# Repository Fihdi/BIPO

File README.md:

# 8hp Dual Bipolar-VCAs / Ring modulators

BIPO consists of two VCAs which can be used individually or locked together to allow for sidechaining / crossfading. Changing the LEVEL, the VCAs can be biased as to allow each section to be used as a ringmodulator. The resulting ringmodulated signal of the input and the CV is available at the BIPO outputs. The VCA outputs are always summed together at the MIX output.

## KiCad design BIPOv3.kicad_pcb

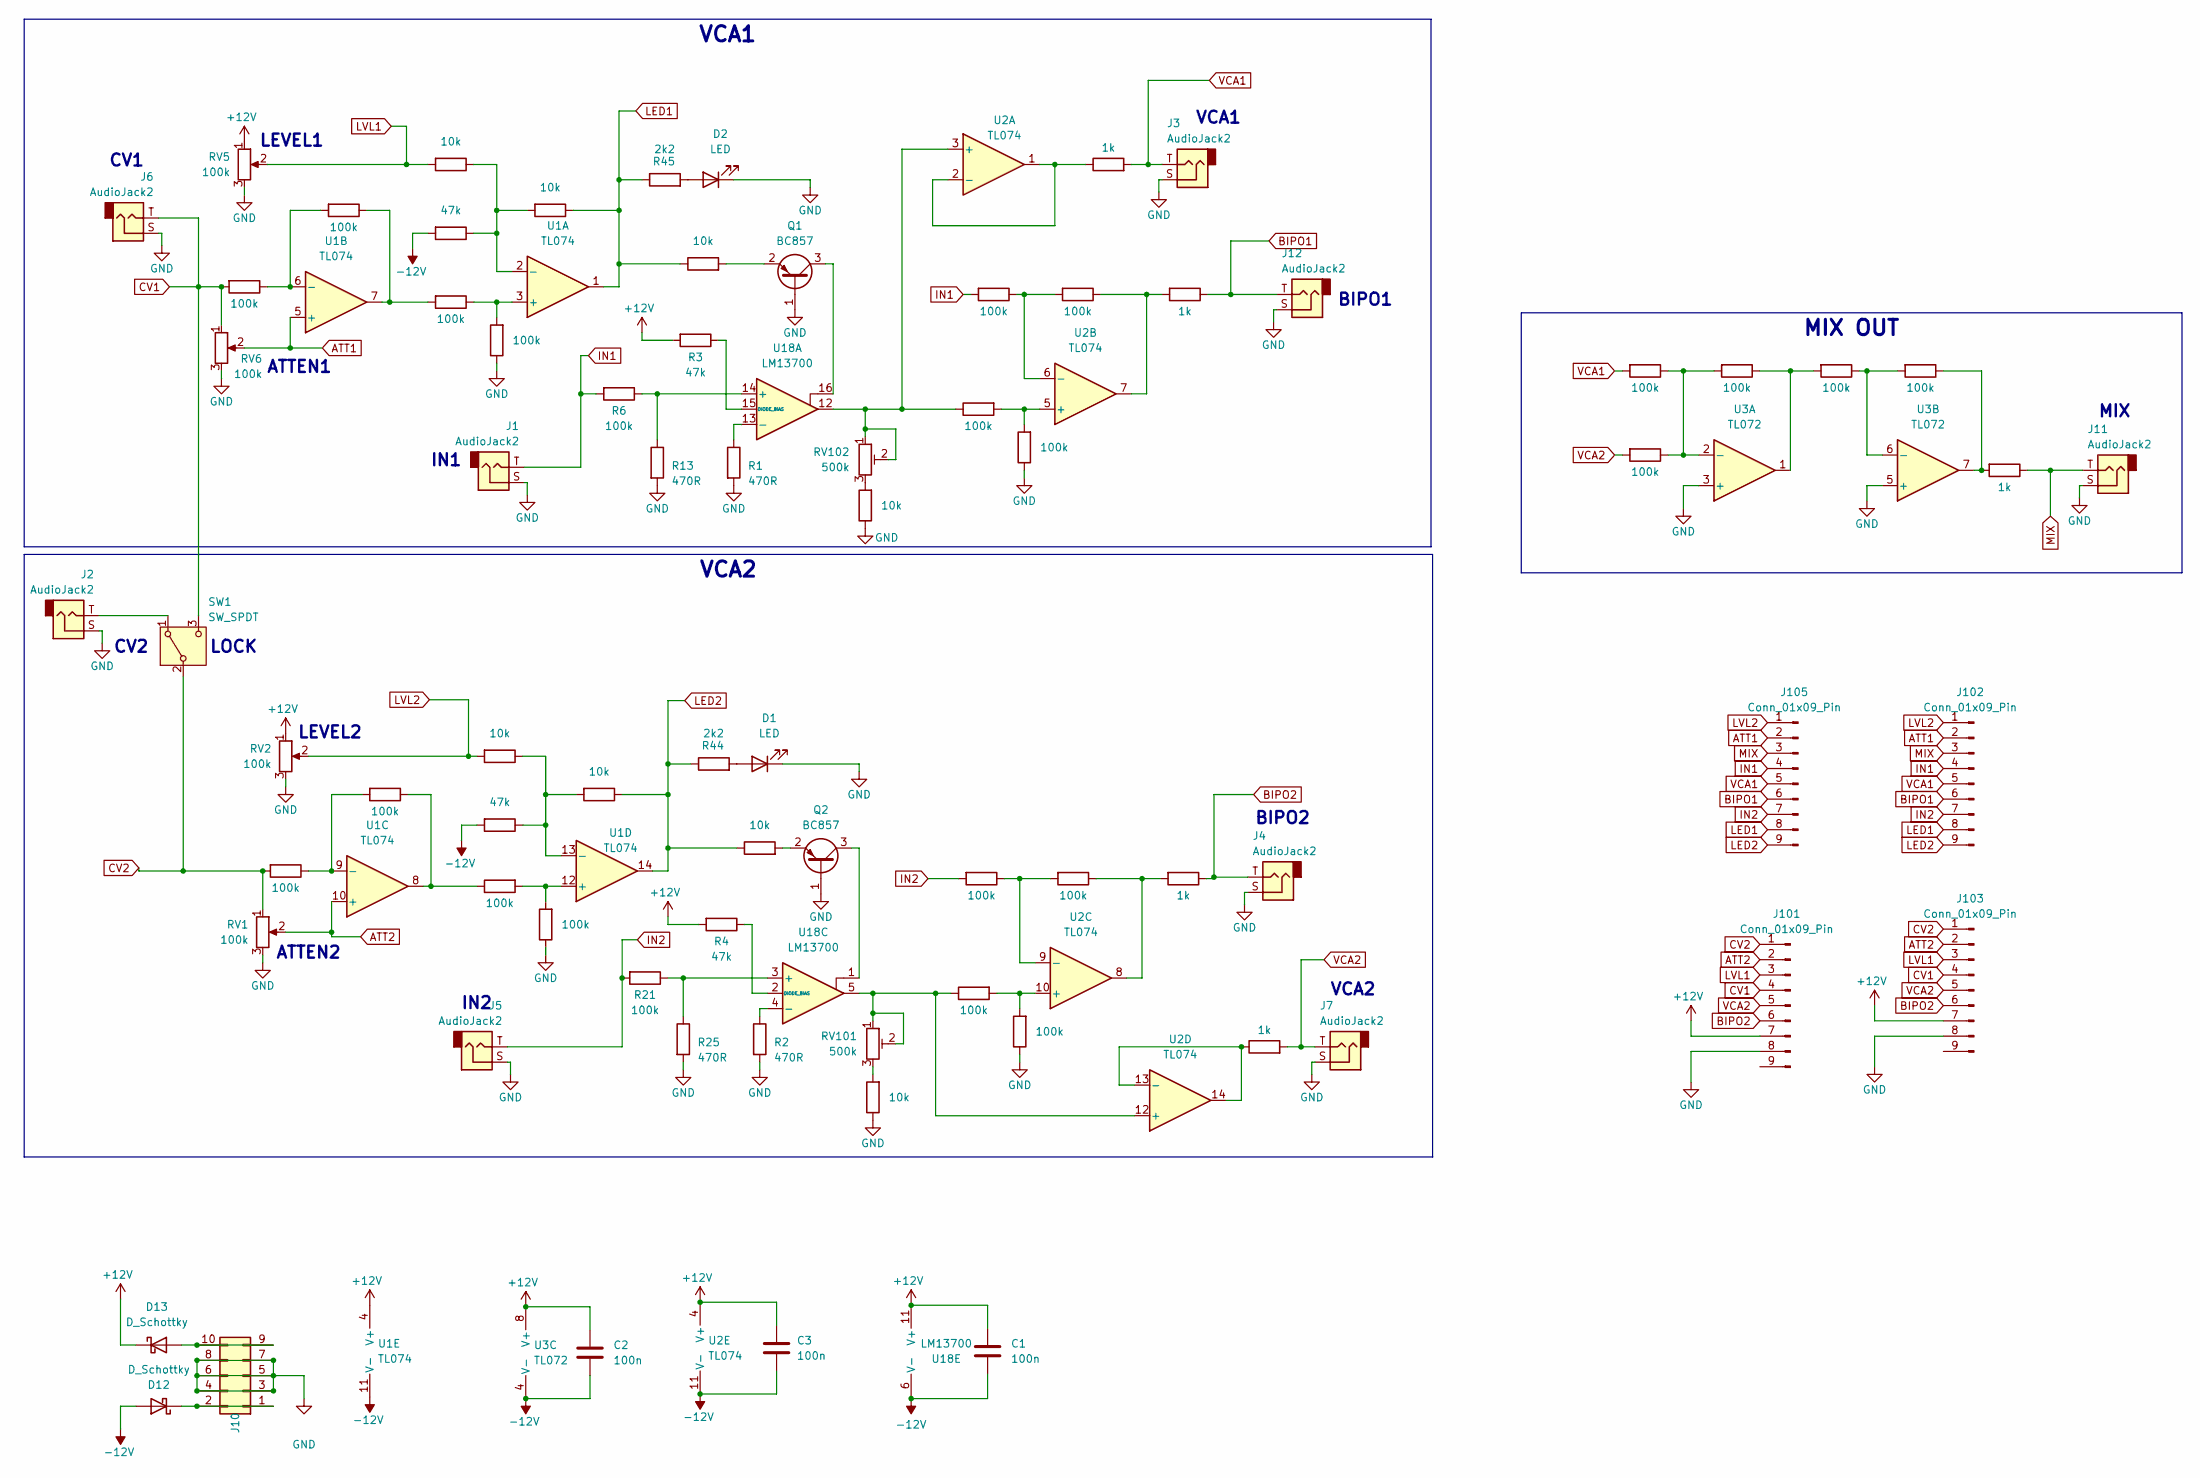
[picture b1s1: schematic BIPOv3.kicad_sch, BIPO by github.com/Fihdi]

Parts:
C1, C2, C3: 100n; C_1206_3216Metric
D1, D2: LED; LED_D3.0mm
D12, D13: D_Schottky; D_SOD-323_HandSoldering
J1, J2, J3, J4, J5, J6, J7, J11, J12: AudioJack2; MonoTRS
J10: Conn_02x05_Odd_Even; IDC-Header_2x05_P2.54mm_Vertical
J101, J102, J103, J105: Conn_01x09_Pin; PinHeader_1x09_P2.54mm_Vertical
Q1, Q2: BC857; SOT-23
R1, R2, R13, R25: 470R; R_1206_3216Metric
R3, R4, R10, R22: 47k; R_1206_3216Metric
R5, R7, R11, R12, R20, R26, R28, R83: 10k; R_1206_3216Metric
R6, R8, R9, R14, R15, R16, R17, R18, R19, R21, R23, R24, R27, R29, R30, R31, R32, R34, R35, R38, R39, R41, R42: 100k; R_1206_3216Metric
R33, R36, R37, R40, R43: 1k; R_1206_3216Metric
R44, R45: 2k2; R_1206_3216Metric
RV1, RV2, RV5, RV6: 100k; Potentiometer_Alpha_RD901F-40-00D_Single_Vertical
RV101, RV102: 500k; Potentiometer_Bourns_3266Y_Vertical
SW1: SW_SPDT; Switch
U1, U2: TL074; SOIC-14_3.9x8.7mm_P1.27mm
U3: TL072; SOIC-8_3.9x4.9mm_P1.27mm
U18: LM13700; SOIC-16_3.9x9.9mm_P1.27mm

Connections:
+12V: C1.1, C2.1, C3.1, D13.1 (K), J101.7, J103.7, R3.2, R4.2, RV2.1, RV5.1, U1.4 (V+), U2.4 (V+), U3.8 (V+), U18.11 (V+)
-12V: C1.2, C2.2, C3.2, D12.2 (A), R10.2, R22.2, U1.11 (V-), U2.11 (V-), U3.4 (V-), U18.6 (V-)
ATT1: J102.2, J105.2, RV6.2, U1.5 (+)
ATT2: J101.2, J103.2, RV1.2, U1.10 (+)
BIPO1: J12.T, J102.6, J105.6, R36.1
BIPO2: J4.T, J101.6, J103.6, R33.1
CV1: J6.T, J101.4, J103.4, R15.2, RV6.1, SW1.3 (C)
CV2: J101.1, J103.1, R18.2, RV1.1, SW1.2 (B)
GND: D1.1 (K), D2.1 (K), J1.S, J2.S, J3.S, J4.S, J5.S, J6.S, J7.S, J10.3, J10.4, J10.5, J10.6, J10.7, J10.8, J11.S, J12.S, J101.8, J103.8, Q1.1 (B), Q2.1 (B), R1.2, R2.2, R5.1, R7.1, R8.1, R13.2, R24.1, R25.2, R39.1, R42.1, RV1.3, RV2.3, RV5.3, RV6.3, U3.3 (+), U3.5 (+)
IN1: J1.T, J102.4, J105.4, R6.2, R17.2
IN2: J5.T, J102.7, J105.7, R21.2, R34.2
LED1: J102.8, J105.8, R11.1, R45.1, R83.1, U1.1
LED2: J102.9, J105.9, R26.1, R28.1, R44.1, U1.14
LVL1: J101.3, J103.3, R12.2, RV5.2
LVL2: J102.1, J105.1, R20.2, RV2.2
MIX: J11.T, J102.3, J105.3, R37.1
unnamed: D1.2 (A), R44.2
unnamed: D2.2 (A), R45.2
unnamed: D12.1 (K), J10.1, J10.2
unnamed: D13.2 (A), J10.9, J10.10
unnamed: Q1.3 (C), U18.16
unnamed: Q1.2 (E), R83.2
unnamed: Q2.3 (C), U18.1
unnamed: Q2.2 (E), R28.2
unnamed: R5.2, RV102.3
unnamed: R7.2, RV101.3
unnamed: R9.2, R14.1, U1.7
unnamed: R16.1, R36.2, U2.7
unnamed: R19.1, R23.1, U1.8
unnamed: R29.1, R30.2, U3.1
unnamed: R31.1, R37.2, U3.7
unnamed: R33.2, R35.1, U2.8
unnamed: J2.T, SW1.1 (A)
unnamed: R8.2, R9.1, U1.3 (+)
unnamed: R10.1, R11.2, R12.1, U1.2 (-)
unnamed: R14.2, R15.1, U1.6 (-)
unnamed: R18.1, R19.2, U1.9 (-)
unnamed: R23.2, R24.2, U1.12 (+)
unnamed: R20.1, R22.1, R26.2, U1.13 (-)
unnamed: R38.1, RV102.1, RV102.2, U2.3 (+), U18.12
unnamed: R40.1, U2.1, U2.2 (-)
unnamed: R38.2, R39.2, U2.5 (+)
unnamed: R16.2, R17.1, U2.6 (-)
unnamed: R41.2, R42.2, U2.10 (+)
unnamed: R34.1, R35.2, U2.9 (-)
unnamed: R41.1, RV101.1, RV101.2, U2.12 (+), U18.5
unnamed: R43.1, U2.13 (-), U2.14
unnamed: R27.1, R29.2, R32.1, U3.2 (-)
unnamed: R30.1, R31.2, U3.6 (-)
unnamed: R6.1, R13.1, U18.14 (+)
unnamed: R1.1, U18.13 (-)
unnamed: R3.1, U18.15 (DIODE_BIAS)
unnamed: R21.1, R25.1, U18.3 (+)
unnamed: R2.1, U18.4 (-)
unnamed: R4.1, U18.2 (DIODE_BIAS)
VCA1: J3.T, J102.5, J105.5, R27.2, R40.2
VCA2: J7.T, J101.5, J103.5, R32.2, R43.2

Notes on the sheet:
BIPO2
CV1
LEVEL1
VCA1
IN2
LEVEL2
LOCK
IN1
ATTEN1
VCA2
BIPO1
ATTEN2
MIX
CV2
MIX OUT

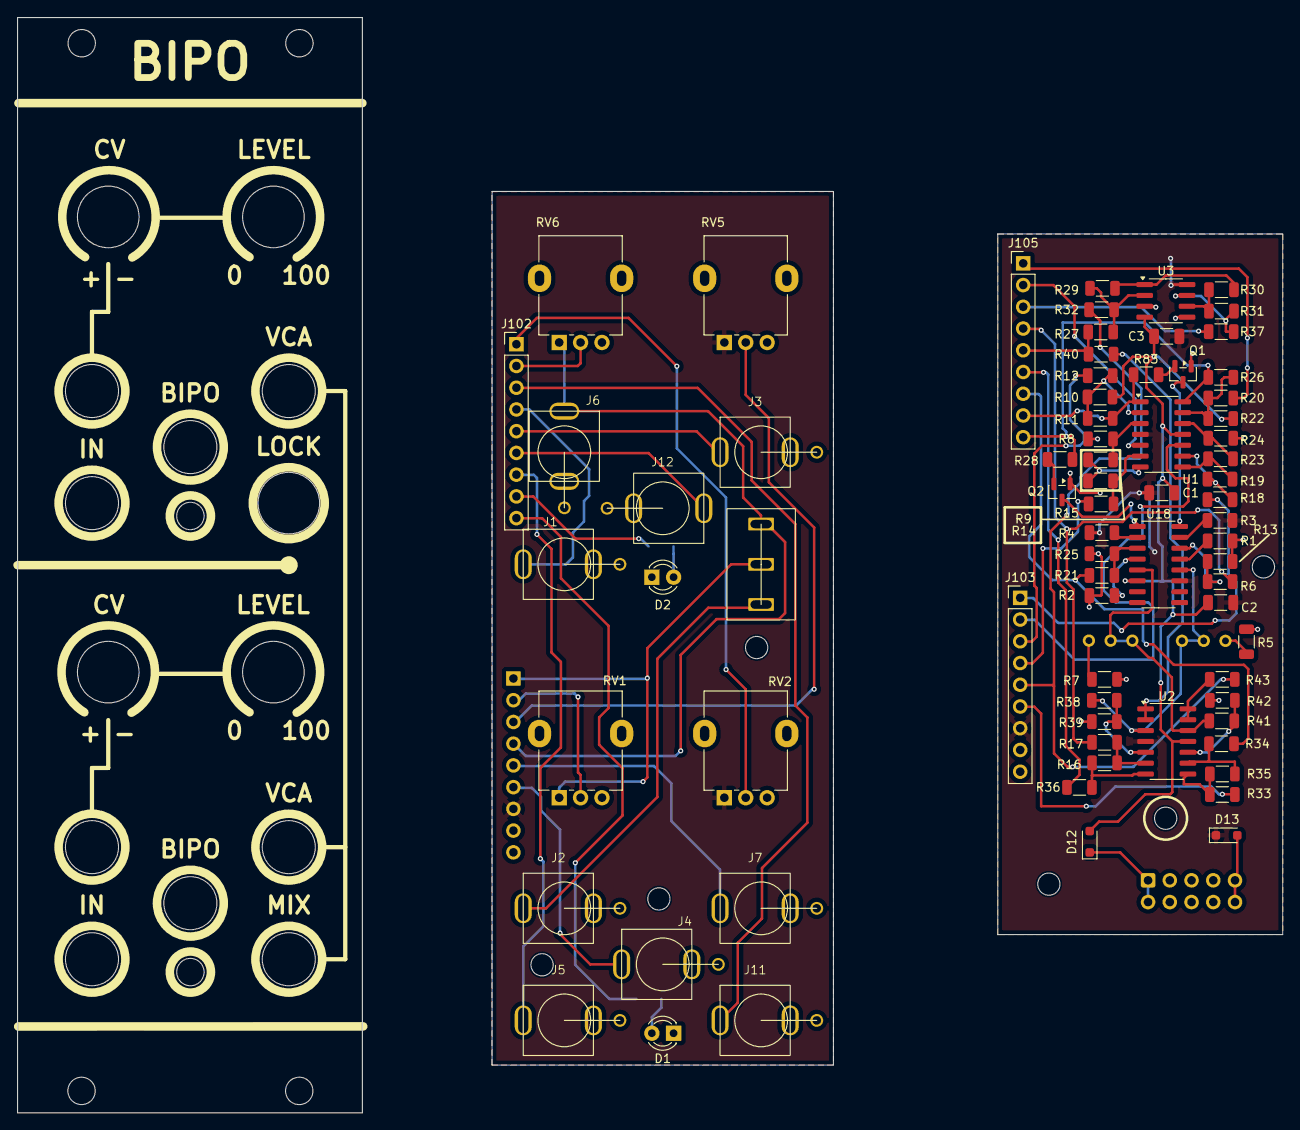
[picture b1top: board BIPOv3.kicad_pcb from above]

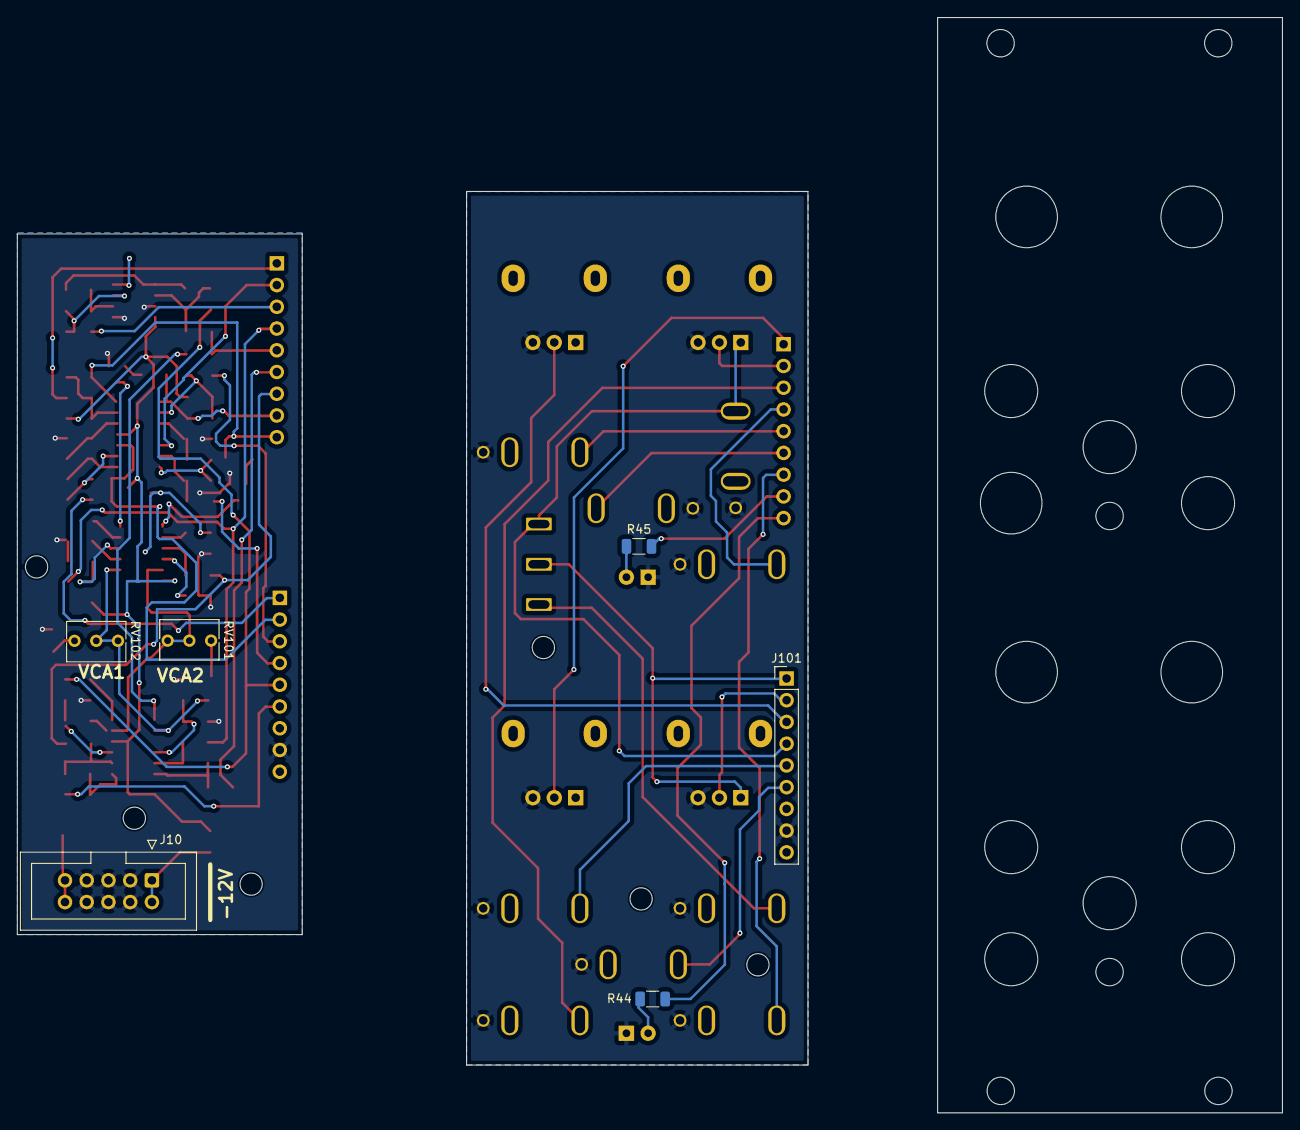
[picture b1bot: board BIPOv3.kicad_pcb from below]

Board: 2 copper layers, 147.8 x 128.0 mm, 80 parts (6 on the bottom side), 57 nets.

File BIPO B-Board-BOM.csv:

"Reference","Qty","Value","DNP","Exclude from BOM","Exclude from Board","Footprint"
"C1,C2,C3","3","100n","","","","Capacitor_SMD:C_1206_3216Metric"
"D12,D13","2","D_Schottky","","","","Diode_SMD:D_SOD-323_HandSoldering"
"J10","1","Conn_02x05_Odd_Even","","","","Connector_IDC:IDC-Header_2x05_P2.54mm_Vertical"
"J103,J105","2","Conn_01x09_Pin","","","","Connector_PinHeader_2.54mm:PinHeader_1x09_P2.54mm_Vertical"
"Q1,Q2","2","BC857","","","","Package_TO_SOT_SMD:SOT-23"
"R1,R2,R13,R25","4","470R","","","","Resistor_SMD:R_1206_3216Metric"
"R3,R4,R10,R22","4","47k","","","","Resistor_SMD:R_1206_3216Metric"
"R5,R7,R11,R12,R20,R26,R28,R83","8","10k","","","","Resistor_SMD:R_1206_3216Metric"
"R6,R8,R9,R14,R15,R16,R17,R18,R19,R21,R23,R24,R27,R29,R30,R31,R32,R34,R35,R38,R39,R41,R42","23","100k","","","","Resistor_SMD:R_1206_3216Metric"
"R33,R36,R37,R40,R43","5","1k","","","","Resistor_SMD:R_1206_3216Metric"
"RV101,RV102","2","500k","","","","Potentiometer_THT:Potentiometer_Bourns_3266Y_Vertical"
"U1,U2","2","TL074","","","","Package_SO:SOIC-14_3.9x8.7mm_P1.27mm"
"U3","1","TL072","","","","Package_SO:SOIC-8_3.9x4.9mm_P1.27mm"
"U18","1","LM13700","","","","Package_SO:SOIC-16_3.9x9.9mm_P1.27mm"

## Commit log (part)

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2026-06-01 Create LICENSE
